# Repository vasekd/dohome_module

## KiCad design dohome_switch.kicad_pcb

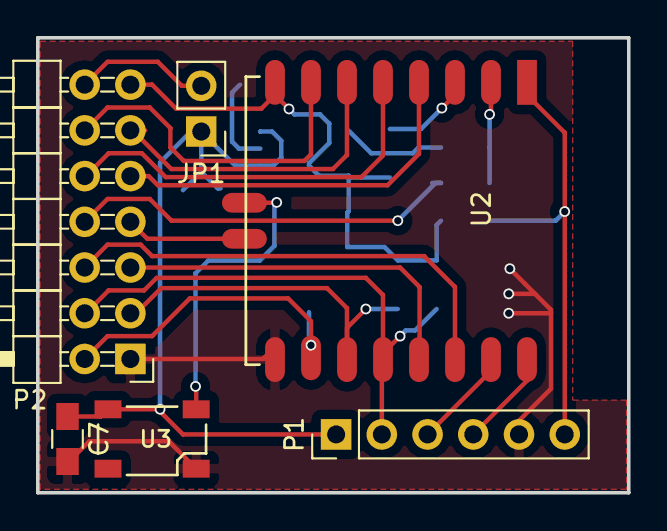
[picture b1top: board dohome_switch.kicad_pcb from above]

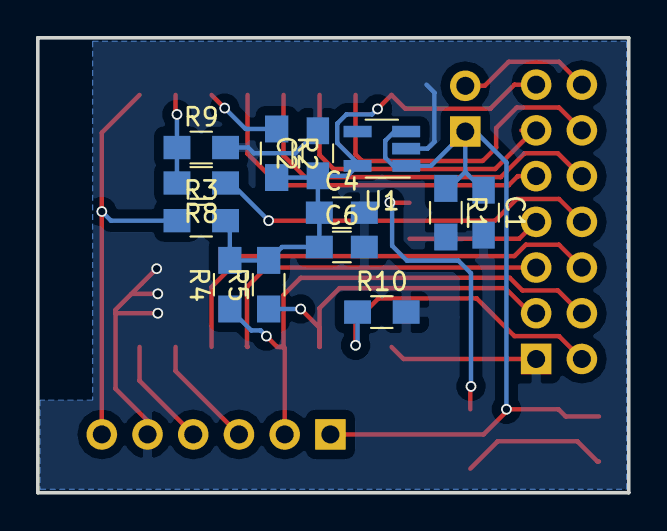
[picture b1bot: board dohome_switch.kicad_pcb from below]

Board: 2 copper layers, 32.8 x 25.3 mm, 19 parts (13 on the bottom side), 21 nets.

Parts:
C1, C2: 1uF; C_0805_HandSoldering
C4: 10uF; C_0805_HandSoldering
C6: 100nF; C_0805_HandSoldering
C7: 0.1uF; C_0805_HandSoldering
JP1: JP1; Pin_Header_Straight_1x02_Pitch2.54mm
P1: FTDI; Socket_Strip_Straight_1x06_Pitch2.54mm
P2: CONN_02X07; Pin_Header_Angled_2x07_Pitch2.54mm
R1, R9, R10: 100k; R_0805_HandSoldering
R2, R3, R4, R5: 10k; R_0805_HandSoldering
R8: 220k; R_0805_HandSoldering
U1: RT9013-33GB; SOT-23-5_HandSoldering
U2: ESP-12E
U3: WS2812B; WS2812B_smallsilk

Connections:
+3V3: C2.1, C4.1, C6.1, P2.13, R2.2, R3.2, R4.2, R5.2, U1.5, U2.8
/A0: P2.8, R8.1
/ADC: R8.2, R9.1, U2.2
/CH_PD: R2.1, U2.3
/GPIO0: P1.2, P2.4, R4.1, U2.12
/GPIO2: P2.3, R5.1, U2.11
/GPIO4: P2.5, U2.13
/GPIO5: P2.6, U2.14
/GPIO9: U2.19, U3.4
/GPIO10: P2.7, U2.20
/GPIO12: P2.11, U2.6
/GPIO13: P2.12, U2.7
/GPIO14: P2.10, U2.5
/GPIO15: P2.2, R10.1, U2.10
/GPIO16: P2.9, U2.4
/PWR: C1.1, C7.1, JP1.1, P1.1, R1.1, U1.1, U1.3, U3.1
/RESET: P1.6, R3.1, U2.1
/RXD: P1.3, U2.15
/TXD: P1.4, U2.16
GND: C1.2, C2.2, C4.2, C6.2, C7.2, P1.5, P2.1, R1.2, R9.2, R10.2, U1.2, U2.9, U3.3
unnamed: JP1.2, P2.14

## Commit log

2017-04-15 CODE: version 1.0
2017-05-11 CODE: new version with ftdi
2017-05-11 CODE: Without lines
2017-05-12 CODE: first version
2017-05-14 CODE: new size of desk
